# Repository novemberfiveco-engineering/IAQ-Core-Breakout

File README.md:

# IAQ-Core
[The IAQ-core Indoor Air Quality Module](https://www.tindie.com/products/novemberfive/iaq-core-sensor-module/) is a low-cost, ultra-compact solution for detecting poor air quality. This module uses micromachined metal oxide semiconductor (MOS) technology to detect a broad range of VOCs while correlating directly with CO2 and TVOC levels in the room.

## Features

- Measure VOC levels 
- Provide CO2- and TVOC equivalent predictions
- Data is available via I2C bus
- The sensor itself is protected by a plastic cap and a filter membrane
- Pull-up resistors are present on the board
- 4 mounting holes allow this breakout to be easily embedded into a project
- Supply Voltage 3.3V
- Board provides a place for connecting rows of 3 pin headers
- Breadboard friendly
- 35.2 x 25.4 mm

For more information about the IAQ-Core please click [here](http://ams.com/eng/Products/Environmental-Sensors/Air-Quality-Sensors)

Note: Please read the I2C addressing instructions carefully. An undefined use of the I2C interface could harm the iAQ-Core module and cause a loss of functionality.

## Note
Choose between IAQ-Core C and - P (continuous & pulsed). 
- pulsed has 9mW power consumption and a measurement interval of 11s. (max).
- continuous has 66mW power consumption and a measurement interval of 1s. (max).

## Where to get?
You can buy this item on Tindie from the [November Five's hardware shop](https://www.tindie.com/products/novemberfive/iaq-core-sensor-module/).

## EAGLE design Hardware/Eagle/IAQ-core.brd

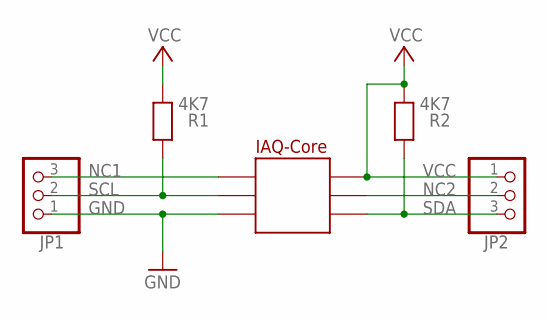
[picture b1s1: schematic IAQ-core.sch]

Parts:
IAQ-CORE: IAQ-CORE
JP1, JP2: PINHD-1X3; 1X03
R1, R2: 4K7; R0603

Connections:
GND: IAQ-CORE.GND, JP1.1
NC1: IAQ-CORE.NC1, JP1.3
NC2: IAQ-CORE.NC2, JP2.2
SCL: IAQ-CORE.SCL, JP1.2, R1.1
SDA: IAQ-CORE.SDA, JP2.3, R2.1
VCC: IAQ-CORE.VCC, JP2.1, R1.2, R2.2

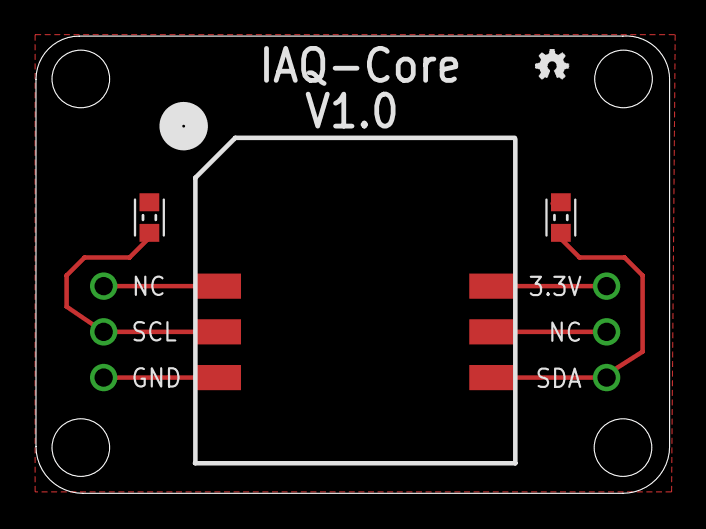
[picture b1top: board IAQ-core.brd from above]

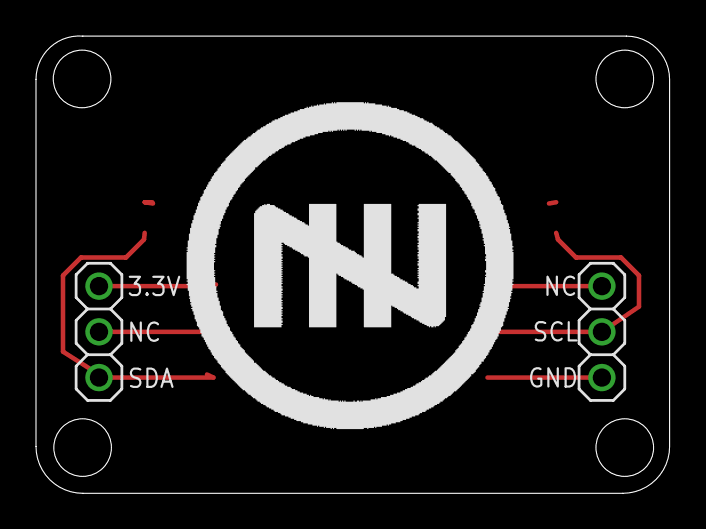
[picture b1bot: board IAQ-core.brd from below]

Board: 2 copper layers, 35.2 x 25.4 mm, 7 parts (2 on the bottom side), 6 nets.

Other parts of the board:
U$1: LOGO-NOVEMERFIVE-2,5SCALE-MIRROR
U$2: LOGO-OSHWA

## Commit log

2017-05-10 Added readme
2017-05-15 Added project library
2017-05-16 Added bom

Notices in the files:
parts and their libraries:
SparkFun-Aesthetics: Licensing: Creative Commons ShareAlike 4.0 International - https://creativecommons.org/licenses/by-sa/4.0
